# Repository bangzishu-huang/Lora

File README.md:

# Lora
A custom custom Meshtastic-enabled LORA board to advance my pcb making skills.

I learned a lot through this process especially how a radio works through a pcb! It also taught me how to occasionally save on KiCAD (because it crashed on me and made me lose all my work).

# 3D View
This was done in KiCAD's 3d viewer.

# PCB
Everything here was also done on KiCAD as well.

- Schematic
- 
- PCB Design
- 

# BOM (Bill of Materials)
| Quantity | Part Name        | Link                                                                                                |
|----------|------------------|-----------------------------------------------------------------------------------------------------|
| 4        | 100nF Capacitor  | https://uelectronics.com/producto/c0603x104k050t-capacitor-ceramico-0603-100nf-50v/                 |
| 2        | Button           | https://www.amazon.com.mx/pulsador-interruptor-momentáneo-microinterruptor-automático/dp/B0DBGMNQV1 |
| 2        | 10nF Capacitor   | https://uelectronics.com/producto/capacitor-ceramico-0805-10uf-16v-cl21a106koqnnne/                 |
| 2        | 5.1k Resistors   | https://www.digikey.com.mx/es/products/detail/yageo/RC0603FR-135K1L/14008317                        |
| 2        | 10k Resistors    | https://uelectronics.com/producto/resistor-10k-ohm-1-10w-smd-0603-rc0603fr-0710kl/                  |
| 1        | 3.3v Regulator   | https://www.digikey.com.mx/es/products/detail/evvo/AMS1117-3.3/22482148                             |
| 1        | 15µH Inductor    | https://www.mouser.mx/ProductDetail/TAIYO-YUDEN/LSXND4040KKL150MDG                                  |
| 1        | USB-C            | https://es.aliexpress.com/item/1005005371954812.html                                                |
| 1        | SX1262           | https://www.amazon.com.mx/Taidacent-transceptor-inalámbrico-Transceptor-aplicaciones/dp/B083NVDGGD  |
| 1        | ESP32-S3-WROOM-1 | https://www.digikey.com.mx/es/products/detail/espressif-systems/ESP32-S3-WROOM-1U-N8R8/16162638     |

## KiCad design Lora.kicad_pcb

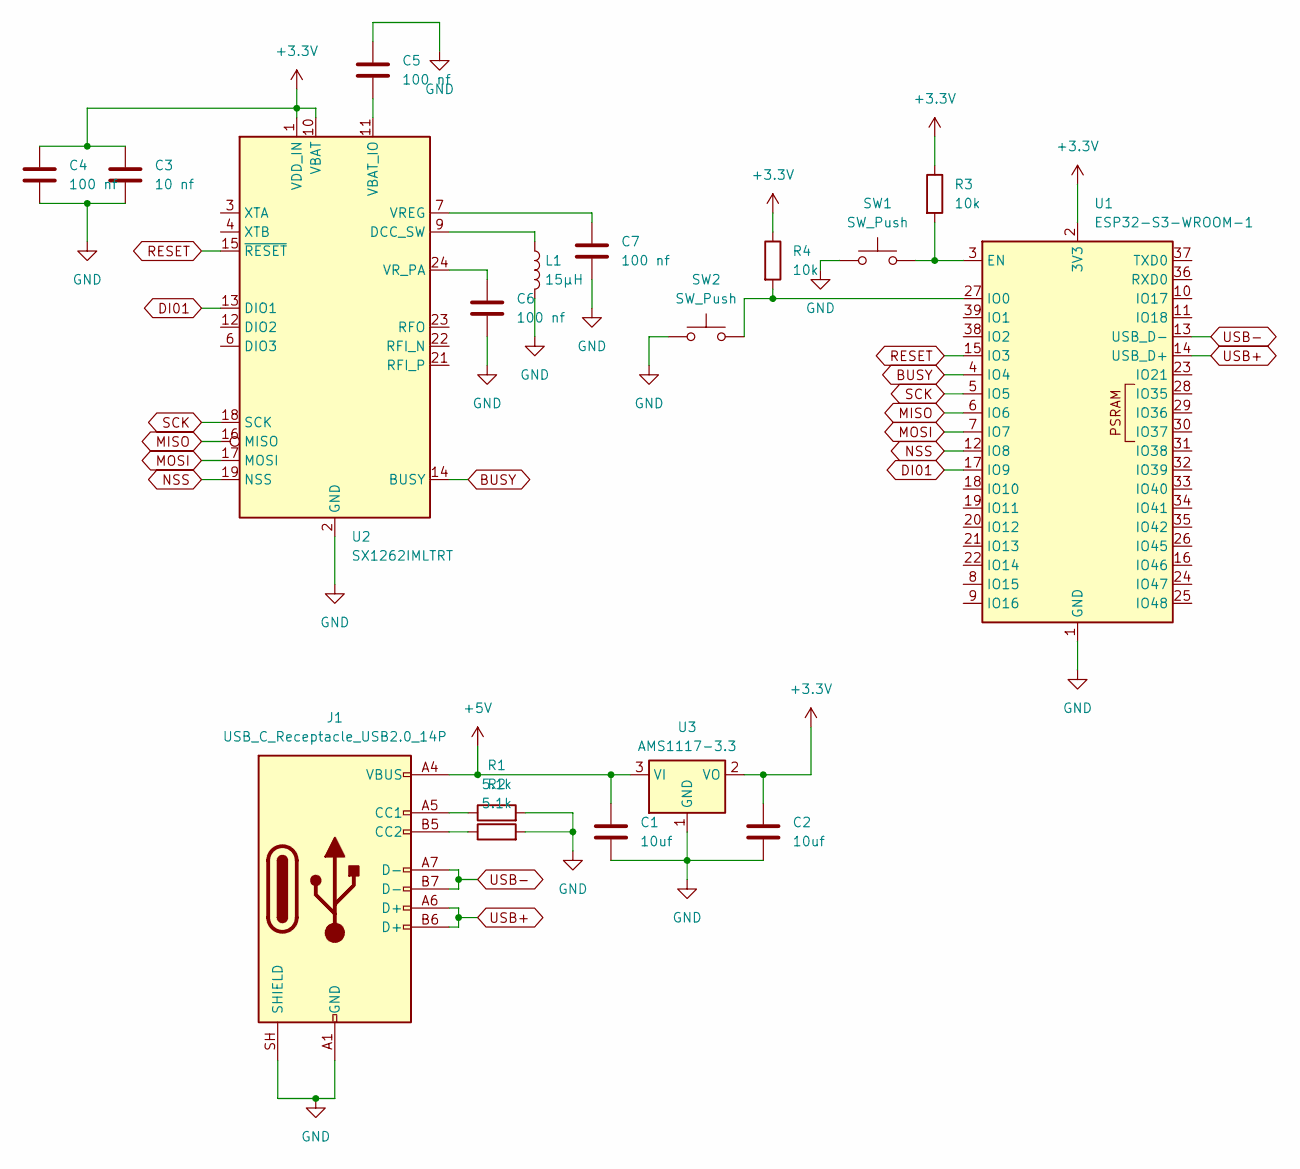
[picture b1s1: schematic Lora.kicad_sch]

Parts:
C1, C2: 10uf; C_0402_1005Metric
C3: 10 nf; C_0402_1005Metric
C4, C5, C6, C7: 100 nf; C_0402_1005Metric
J1: USB_C_Receptacle_USB2.0_14P; USB_C_Receptacle_HRO_TYPE-C-31-M-12
L1: 15µH; L_0201_0603Metric
R1, R2: 5.1k; R_0402_1005Metric
R3, R4: 10k; R_0402_1005Metric
SW1, SW2: SW_Push; SW_Push_SPST_NO_Alps_SKRK
U1: ESP32-S3-WROOM-1
U2: SX1262IMLTRT; QFN-24-1EP_4x4mm_P0.5mm_EP2.6x2.6mm
U3: AMS1117-3.3; SOT-223-3_TabPin2

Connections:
+3.3V: C2.1, C3.1, C4.1, R3.1, R4.1, U1.2 (3V3), U2.1 (VDD_IN), U2.10 (VBAT), U3.2 (VO)
+5V: C1.1, J1.A4 (VBUS), J1.A9 (VBUS), J1.B4 (VBUS), J1.B9 (VBUS), U3.3 (VI)
BUSY: U1.4 (IO4), U2.14 (BUSY)
DI01: U1.17 (IO9), U2.13 (DIO1)
GND: C1.2, C2.2, C3.2, C4.2, C5.1, C6.2, C7.2, J1.A1 (GND), J1.A12 (GND), J1.B1 (GND), J1.B12 (GND), J1.SH (SHIELD), L1.2, R1.2, R2.2, SW1.1, SW2.1, U1.1 (GND), U1.40 (GND), U1.41 (GND), U2.2 (GND), U2.5 (GND), U2.8 (GND), U2.20 (GND), U2.25 (GND), U3.1 (GND)
MISO: U1.6 (IO6), U2.16 (MISO)
MOSI: U1.7 (IO7), U2.17 (MOSI)
NSS: U1.12 (IO8), U2.19 (NSS)
unnamed: J1.A5 (CC1), R1.1
unnamed: J1.B5 (CC2), R2.1
unnamed: R3.2, SW1.2, U1.3 (EN)
unnamed: R4.2, SW2.2, U1.27 (IO0)
unnamed: L1.1, U2.9 (DCC_SW)
unnamed: C5.2, U2.11 (VBAT_IO)
unnamed: C7.1, U2.7 (VREG)
unnamed: C6.1, U2.24 (VR_PA)
RESET: U1.15 (IO3), U2.15 (~RESET)
SCK: U1.5 (IO5), U2.18 (SCK)
USB+: J1.A6 (D+), J1.B6 (D+), U1.14 (USB_D+)
USB-: J1.A7 (D-), J1.B7 (D-), U1.13 (USB_D-)

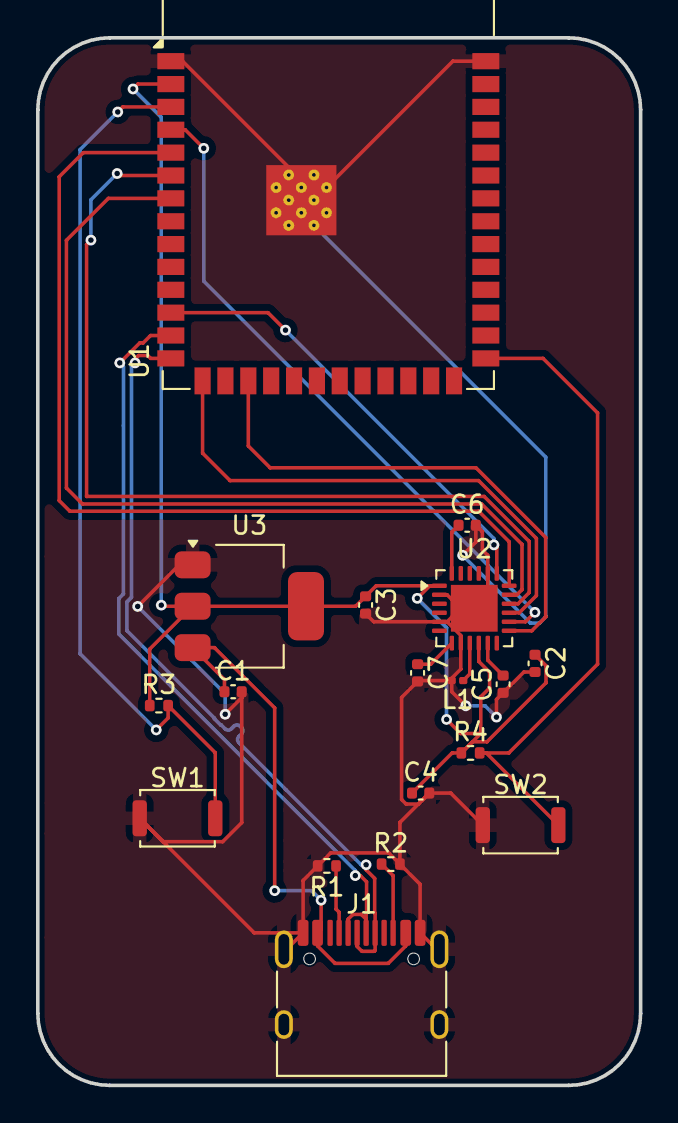
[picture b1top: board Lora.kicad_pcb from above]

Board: 2 copper layers, 33.5 x 58.2 mm, 18 parts (0 on the bottom side), 20 nets.

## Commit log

2026-06-21 added files and organized
2026-06-21 Enhance README with project details and BOM
    Expanded the README with additional details about the project, including a 3D view, PCB design, and a Bill of Materials (BOM).
